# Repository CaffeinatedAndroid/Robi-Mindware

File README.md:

# Robi Mindware (PENDING UPDATES)

Robot control software and board driver for a custom version of the Deagnostini Robi Robot: 
https://www.japantrendshop.com/robi-robot-preassembled-version-p-1622.html

They can also be found for less than $250 on second hand on sites like Mecari japan through Neokyo, along with many other robots: 
https://neokyo.com/en/search/mercari?keyword=robi%20robot&provider=mercari&spid=

This mod and software aims to upgrade generation 1 Robis to support modern software and capabilities and extend the useful life of the robot by allowing anyone who wants cheaper and 
more open avenues into robotics to create a more NAO like robot with cheaper hardware.

This project has kicked off after a period of learning all I could about these robots and similar robots from japan,
since enrolling in a computer science degree, this project and robot will serve as an additional learning aid where I can implement 
what I have learned to create a complete robotics project.

In addition to new software, this mod adds a range of new sensors, custom control boards and lively LCD eyes.
I will eventually make the new driver board compatible with a range of servo brands to allow building from scratch
with more available robotics servos. By working with the restraint of such a small robot, I can focus on smaller components
and create a board that can be used in a larger viariety of diy bots.

Powering up and verifying the new custom breakout, a 3rd revision will be created to address a few issues with the current implementation. The eyes currently run on a C bit banged driver due to SPI and overlay issues on the Orangepi and python bit banging is far too slow, This will be addressed by splitting all signals and using my modified devicetree and overlays.

Some Robi parts have been scanned and modified to allow fitting of new hardware with minimal to no damage of the original parts.

The main software is written in python, it sends ID and position commands to a C++ driver on the ESP32 C3 mini.
The ESP32 then processes commands and sends them to the servo bus, daisy chaining is working.

NOTE: The ESP32 will be swapped with a custom RP2040 board.

### Example Command:
```
ID:ANGLE
12:130
15:30
```

Testing with a single communication bus, timing issues and missed messages are an issue that will be resolved with the RP2350B PIO that will allow dedicated channels for each servo chain.

Here timing issues are very clear. There was lots of funny and awkward runs where I was able to at least guage the next step I needed to take.

Development on a RP2350B based microcontroller board is under development and is waiting for some additional validation before I order the boards to be made. This lets me split each servo chain into dedicated channels, that way parts of the robot dont have communications interupted as this could be bad, ie: the legs.

## Hardware:
- Robi servo test board (I will link to an alternative that emulates the same functions in future. It is for setting the ID and testing the motor)
- ESP32 C3 Mini NOTE: FOR INITIAL DEVELOPMENT
- 3.3v-5v Bi-directional logic converter (C3 mini outputs 3.3v logic while the servo requires 5v logic, bi-directional opens up the possibility of adding servo feedback)
- 5v Power supply
- OrangePi Zero 2w or Raspi Zero 2w (More ram the better, Recommended minimum is 4GB)
- REMAINING PARTS TBC

### Picking The Robot:
- Robi 1 or 2 
When selecting a Robi, pick a damaged one or a hand assembled one. There is no point in ruining a good unit when you will need to dissasemble it anyway.
Many Robis have dirty contacts, dry servos, damaged or loose servo cables and maybe sometimes a servo that "Forgot" its settings.
By picking a Robi needing some TLC, you will learn far more and not feel guilt for possibly destroying a functional unit.

## Libraries:
- Panda3D
- Numpy
- OpenCV
- Matplotlib
- Tkinter
- Pandas

## Acknowledgments
The following blog from Japan has proven invaluable, The person behind it deserves lots of credit as they have learned a lot of the harder lessons.
Give them a visit and a thanks if you find it useful.

The site is in Japanese so use google translate if needed. They also have a youtube channel.
- https://www.mcc.mbsrv.net/robox/index.html
- https://www.youtube.com/@craftoyaji

## Additional Useful Sites

I will continue to add more

https://win.adrirobot.it/menu_new/index/index_robi.htm

https://it.emcelettronica.com/levaluation-kit-xmc-2go-di-infineon-come-scheda-sensori-i-robot-robi

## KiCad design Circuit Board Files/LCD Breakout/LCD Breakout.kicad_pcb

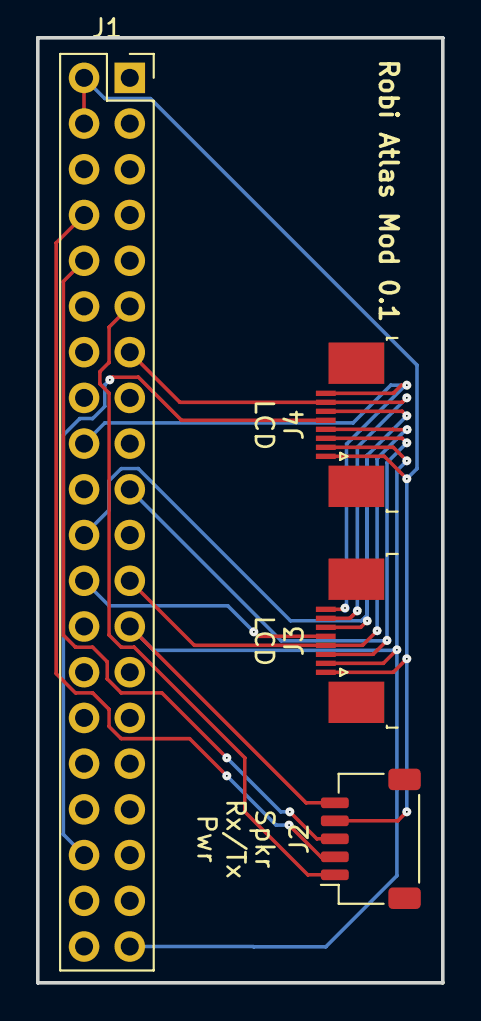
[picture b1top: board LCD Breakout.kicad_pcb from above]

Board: 2 copper layers, 22.5 x 52.5 mm, 4 parts (0 on the bottom side), 13 nets.

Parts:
J1: GPIO; PinSocket_2x20_P2.54mm_Vertical
J2: Conn_01x05_Socket; JST_SH_SM05B-SRSS-TB_1x05-1MP_P1.00mm_Horizontal
J3, J4: Conn_01x08_Socket; TE_0-1734839-8_1x08-1MP_P0.5mm_Horizontal

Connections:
+3V3: J1.1, J1.17
+5V: J1.2, J1.4, J2.4, J3.1, J4.1
/GPIO8/SPI0.CE0: J1.24, J3.5
/GPIO10/SPI0.MOSI: J1.19, J3.3, J4.3
/GPIO11/SPI0.SCLK: J1.23, J3.4, J4.4
/GPIO14/TXD0: J1.8, J2.2
/GPIO15/RXD0: J1.10, J2.3
/GPIO16: J1.36, J4.5
/GPIO17: J1.11, J2.1
/GPIO24: J1.18, J3.8, J4.8
/GPIO25: J1.22, J3.6, J4.6
/GPIO27: J1.13, J3.7, J4.7
GND: J1.6, J1.9, J1.14, J1.20, J1.25, J1.30, J1.34, J1.39, J2.5, J3.2, J4.2

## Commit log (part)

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2026-05-10 Init
    Initial Commit
2026-05-14 Clean Repository
2026-05-14 Base Development Version
    Majority of core logic is implemented. CURRENTLY ONLY SUPPORTS HEAD SERVOS
    Logic needs to be expanded and merged to the Main application
    Remaining serial busses are to be configured
2026-05-14 Updated Code and cleaned up notes
2026-05-14 Readme updated
2026-05-15 Serial servo Head Movement
2026-05-15 Left 3 as backup
2026-06-01 V0.2
    Message Bus based architecture, basic movement and head tracking a ball
2026-06-01 git ignore
2026-06-01 Update README with diagram and hardware notes
    Added image reference and updated hardware section.
2026-06-01 Fix image path for Robi Servo Layout in README
    Updated image path in README to reflect new directory structure.
2026-06-01 Update Diagram Name
2026-06-01 Rename project to 'Robi Mindware' and update notes
    Updated project name and added notes about hardware changes.
2026-06-01 Fix Trello link in README
    Updated Trello link to an invitation link.
2026-06-01 Update README with Trello board link
    Removed iframe link and added Trello board URL.
2026-06-01 Added RP2040 Servo Board Files
2026-06-01 Rename Folder
2026-06-01 readme edit
2026-06-01 Readme
2026-06-01 Updated Readme
    Added Timeline
2026-06-01 Edit Image
2026-06-01 Added Preview
2026-06-08 Added hardware diagram
2026-06-08 added more sources
